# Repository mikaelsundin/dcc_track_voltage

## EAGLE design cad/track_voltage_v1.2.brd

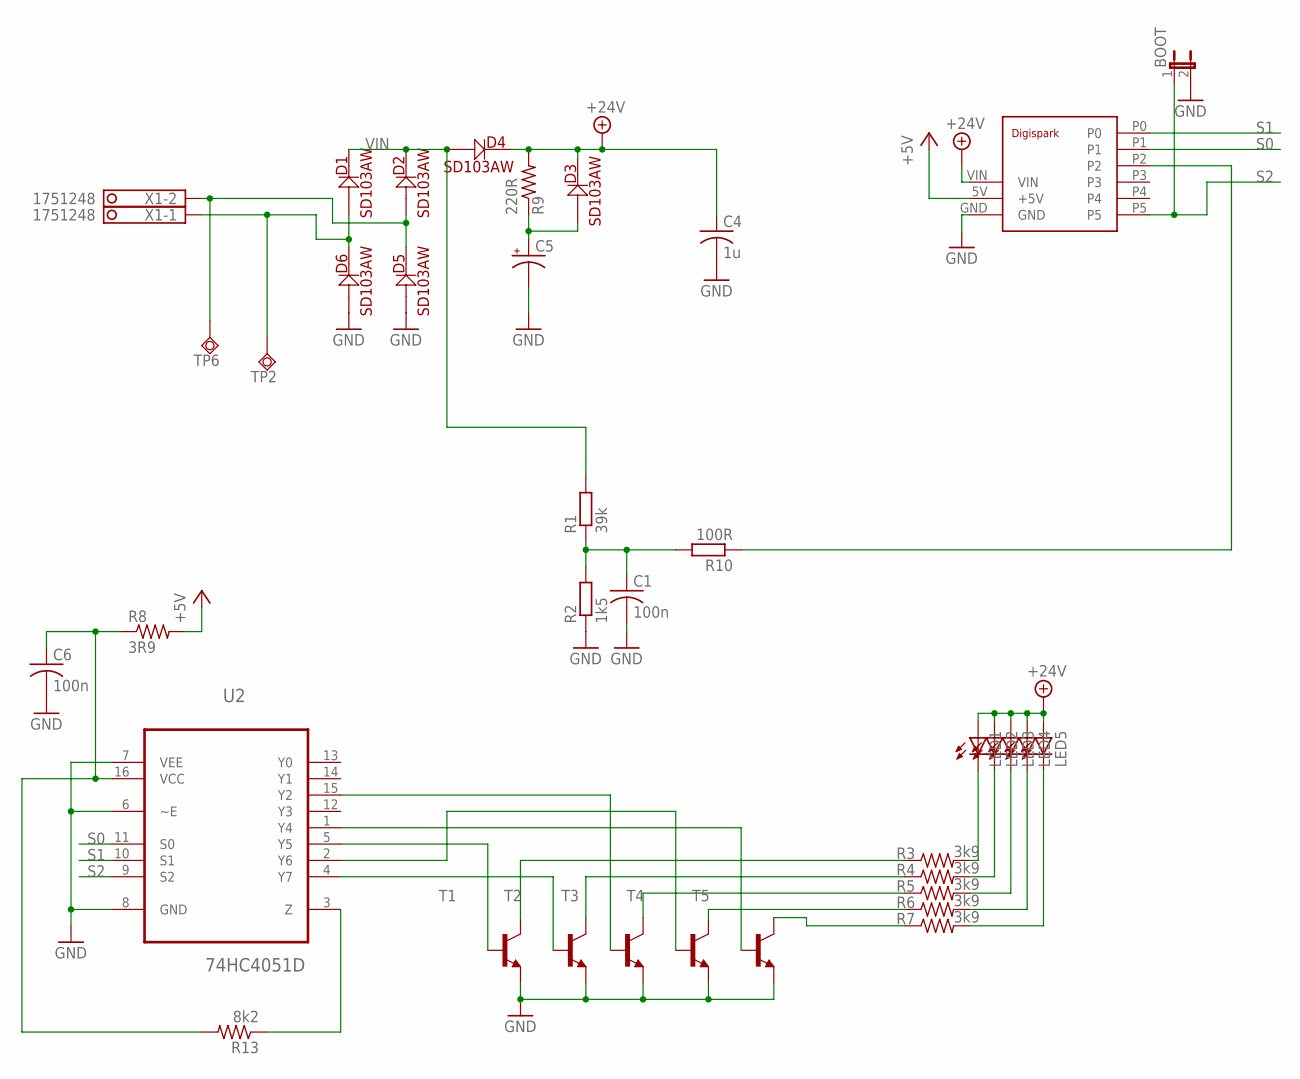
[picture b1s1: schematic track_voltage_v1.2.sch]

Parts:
BOOT: JP1E; JP1
C1, C6: 100n; C0603
C4: 1u; C0603
C5: CPOL-USE3.5-10; E3,5-10
D1, D2, D3, D4, D5, D6: SD103AW; SOD-123
LED1, LED2, LED3, LED4, LED5: LED3MM
R1: 39k; R0603
R2: 1k5; R0603
R3, R4, R5, R6, R7: 3k9; R0805
R8: 3R9; R1206
R9: 220R; R0805
R10: 100R; R0603
R13: 8k2; R0603
T1, T2, T3, T4, T5: BC817-16-NPN-SOT23-BEC; SOT23-BEC
TP2, TP6: TPSQTP20SQ; TP20SQ
U2: 74HC4051D; SOIC127P600X175-16N
U$2: DIGISPARK; DIGISPARK_78M05
X1: 1751248

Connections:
+5V: R8.2, U$2.5V (+5V)
+24V: C4.1, D3.-, D4.-, LED1.A, LED2.A, LED3.A, LED4.A, LED5.A, R9.2, U$2.VIN
GND: BOOT.2, C1.2, C4.2, C5.-, C6.2, D5.+, D6.+, R2.1, T1.E, T2.E, T3.E, T4.E, T5.E, U2.6 (~E), U2.7 (VEE), U2.8 (GND), U$2.GND
unnamed: R10.1, U$2.P2
unnamed: C6.1, R8.1, R13.2, U2.16 (VCC)
unnamed: T2.B, U2.4 (Y7)
unnamed: T1.B, U2.5 (Y5)
unnamed: LED1.K (C), R3.2
unnamed: C5.+, D3.+, R9.1
unnamed: R3.1, T1.C
unnamed: R4.1, T2.C
unnamed: R5.1, T3.C
unnamed: R6.1, T4.C
unnamed: R7.1, T5.C
unnamed: LED2.K (C), R4.2
unnamed: LED3.K (C), R5.2
unnamed: LED4.K (C), R6.2
unnamed: LED5.K (C), R7.2
unnamed: D2.+, D5.-, TP6.TP, X1.2
unnamed: C1.1, R1.1, R2.2, R10.2
unnamed: T3.B, U2.15 (Y2)
unnamed: D1.+, D6.-, TP2.TP, X1.1
unnamed: T4.B, U2.2 (Y6)
unnamed: T5.B, U2.1 (Y4)
unnamed: R13.1, U2.3 (Z)
S0: U2.11 (S0), U$2.P1
S1: U2.10 (S1), U$2.P0
S2: BOOT.1, U2.9 (S2), U$2.P5
VIN: D1.-, D2.-, D4.+, R1.2

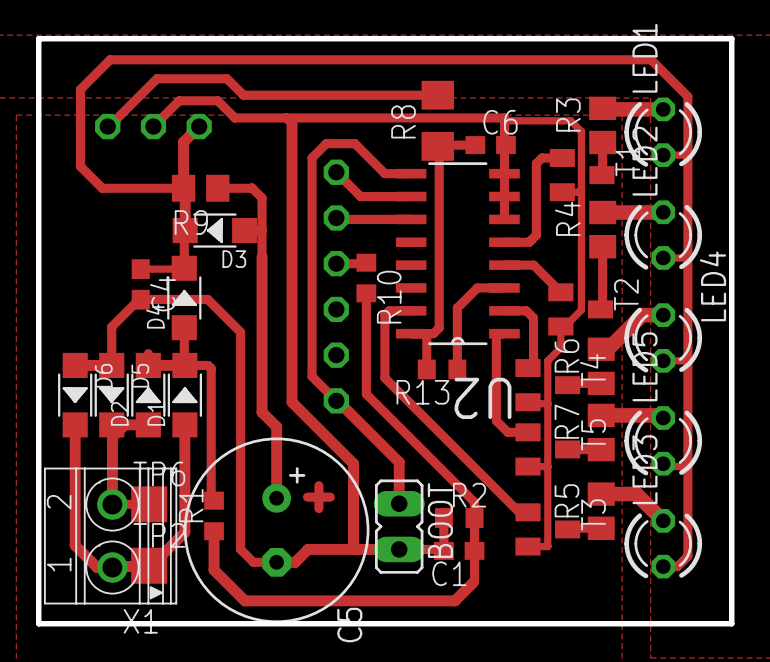
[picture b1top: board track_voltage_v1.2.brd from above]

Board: 2 copper layers, 38.5 x 32.5 mm, 37 parts (1 on the bottom side), 29 nets.

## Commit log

2019-07-02 Initial commit.
2020-02-01 Added some docs, updated code. Updated schematic to use PB5.
2020-02-01 Removed unused textfile.
